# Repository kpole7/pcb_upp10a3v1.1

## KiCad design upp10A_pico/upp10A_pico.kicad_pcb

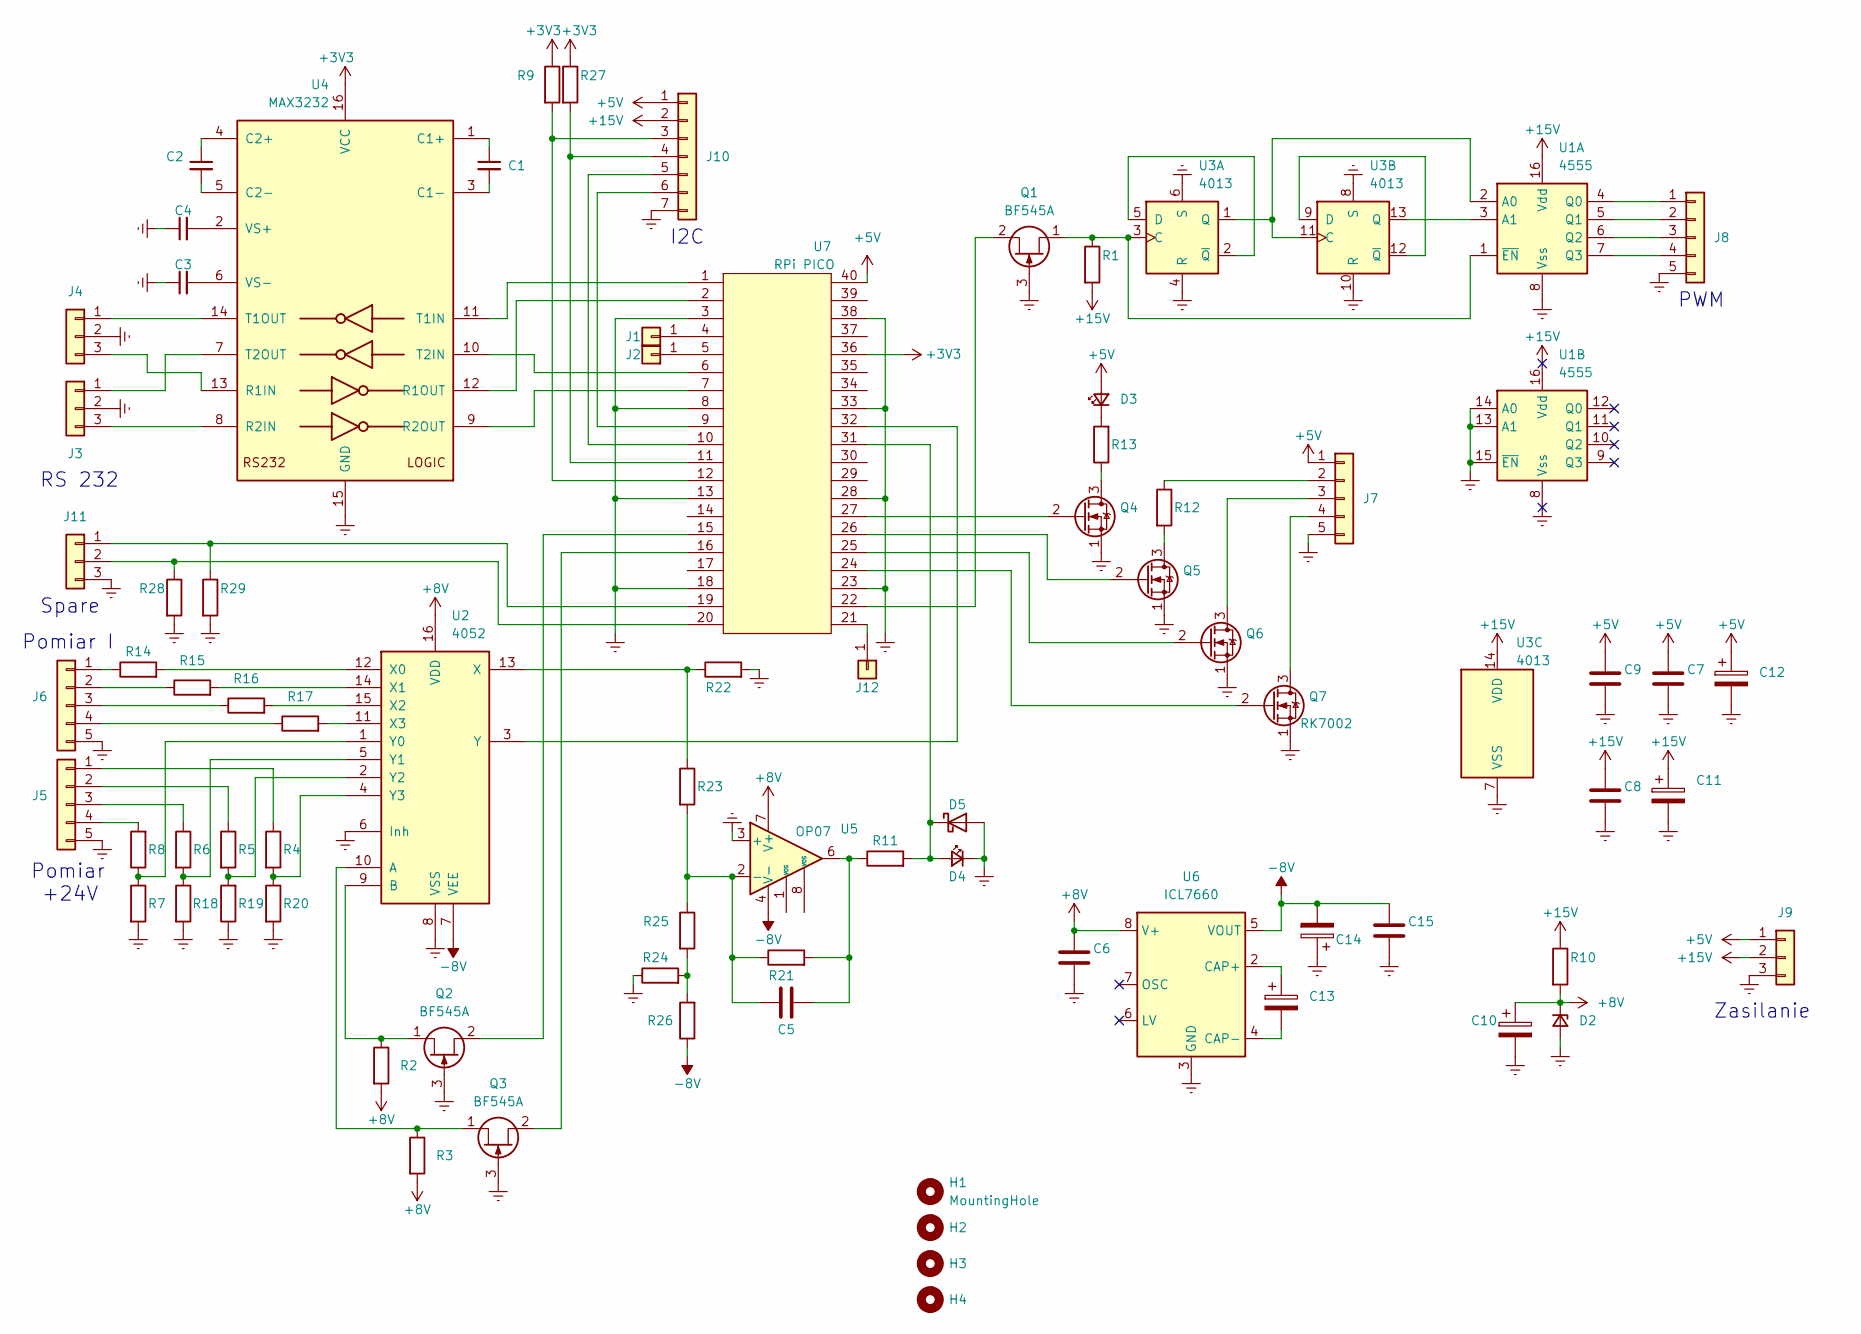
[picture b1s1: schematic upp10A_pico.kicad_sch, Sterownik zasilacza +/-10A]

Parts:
C1, C2, C3, C4: C_Small; C_0805_2012Metric_Pad1.18x1.45mm_HandSolder
C5: C; R_0805_2012Metric_Pad1.20x1.40mm_HandSolder
C6, C7, C8, C9, C15: C; C_0805_2012Metric_Pad1.18x1.45mm_HandSolder
C10, C11, C12, C13, C14: C_Polarized; CP_Radial_D6.3mm_P2.50mm
D2: D_Zener_Small; D_DO-34_SOD68_P7.62mm_Horizontal
D3: LED_Small; D_0805_2012Metric_Pad1.15x1.40mm_HandSolder
D4: LED_Small; D_5KP_P10.16mm_Horizontal
D5: BAT41; D_DO-35_SOD27_P7.62mm_Horizontal
H1, H2, H3, H4: MountingHole; MountingHole_3.2mm_M3_Pad
J1, J2, J12: Conn_01x01; Pin_D1.0mm_L10.0mm
J3, J4, J9, J11: Conn_01x03; PinHeader_1x03_P2.54mm_Vertical
J5, J6, J7, J8: Conn_01x05; PinHeader_1x05_P2.54mm_Vertical
J10: Conn_01x07; PinHeader_1x07_P2.54mm_Vertical
Q1, Q2, Q3: BF545A; SOT-23
Q4, Q5, Q6, Q7: RK7002; SOT-23
R1, R2, R3, R4, R5, R6, R7, R8, R9, R10, R11, R12, R13, R14, R15, R16, R17, R18, R19, R20, R21, R22, R23, R24, R25, R26, R27, R28, R29: R; R_0805_2012Metric_Pad1.20x1.40mm_HandSolder
U1: 4555; DIP-16_W7.62mm
U2: 4052; DIP-16_W8.89mm_SMDSocket_LongPads
U3: 4013; DIP-14_W7.62mm
U4: MAX3232; SOIC-16_3.9x9.9mm_P1.27mm
U5: OP07; DIP-8_W7.62mm
U6: ICL7660; DIP-8_W7.62mm
U7: RPi PICO; DIP-40_W700mils

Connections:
+3V3: R9.1, R27.1, U4.16 (VCC), U7.36
+5V: C7.1, C9.1, C12.1, D3.2 (A), J7.1, J9.1, J10.1, U7.40
+8V: C6.1, C10.1, D2.1 (K), R2.2, R3.2, R10.2, U2.16 (VDD), U5.7 (V+), U6.8 (V+)
+15V: C8.1, C11.1, J9.2, J10.2, R1.2, R10.1, U1.16 (Vdd), U3.14 (VDD)
-8V: C14.2, C15.1, R26.1, U2.7 (VEE), U5.4 (V-), U6.5 (VOUT)
GNDREF: C3.1, C4.1, C6.2, C7.2, C8.2, C9.2, C10.2, C11.2, C12.2, C14.1, C15.2, D2.2 (A), D4.1 (K), D5.2 (A), J3.2, J4.2, J5.5, J6.5, J7.5, J8.5, J9.3, J10.7, J11.3, Q1.3 (G), Q2.3 (G), Q3.3 (G), Q4.1 (S), Q5.1 (S), Q6.1 (S), Q7.1 (S), R7.2, R18.2, R19.1, R20.2, R22.2, R24.1, R28.2, R29.2, U1.8 (Vss), U1.13 (A1), U1.14 (A0), U1.15 (~EN), U2.6 (Inh), U2.8 (VSS), U3.4 (R), U3.6 (S), U3.7 (VSS), U3.8 (S), U3.10 (R), U4.15 (GND), U5.3 (+), U6.3 (GND), U7.3, U7.8, U7.13, U7.18, U7.23, U7.28, U7.33, U7.38
unnamed: C5.2, R11.1, R21.2, U5.6
unnamed: D3.1 (K), R13.2
unnamed: D4.2 (A), D5.1 (K), R11.2, U7.31
unnamed: J1.1, U7.4
unnamed: J2.1, U7.5
unnamed: J3.1, U4.7 (T2OUT)
unnamed: J3.3, U4.8 (R2IN)
unnamed: J4.1, U4.14 (T1OUT)
unnamed: J4.3, U4.13 (R1IN)
unnamed: J5.1, R4.1
unnamed: J5.2, R5.1
unnamed: J5.3, R6.1
unnamed: J5.4, R8.2
unnamed: J6.1, R14.1
unnamed: J6.2, R15.1
unnamed: J6.3, R16.1
unnamed: J6.4, R17.1
unnamed: J7.2, R12.1
unnamed: J7.3, Q6.3 (D)
unnamed: J7.4, Q7.3 (D)
unnamed: J8.1, U1.4 (Q0)
unnamed: J8.2, U1.5 (Q1)
unnamed: J8.3, U1.6 (Q2)
unnamed: J8.4, U1.7 (Q3)
unnamed: J10.3, R9.2, U7.12
unnamed: J10.4, R27.2, U7.11
unnamed: J10.5, U7.10
unnamed: J10.6, U7.9
unnamed: J11.1, R29.1, U7.19
unnamed: J11.2, R28.1, U7.20
unnamed: J12.1, U7.21
unnamed: Q1.2 (D), U7.22
unnamed: Q1.1 (S), R1.1, U1.1 (~EN), U3.3 (C)
unnamed: Q2.2 (D), U7.15
unnamed: Q2.1 (S), R2.1, U2.9 (B)
unnamed: Q3.2 (D), U7.16
unnamed: Q3.1 (S), R3.1, U2.10 (A)
unnamed: Q4.3 (D), R13.1
unnamed: Q4.2 (G), U7.27
unnamed: Q5.3 (D), R12.2
unnamed: Q5.2 (G), U7.26
unnamed: Q6.2 (G), U7.25
unnamed: Q7.2 (G), U7.24
unnamed: R24.2, R25.2, R26.2
unnamed: U1.2 (A0), U3.1 (Q), U3.11 (C)
unnamed: U1.3 (A1), U3.13 (Q)
unnamed: R14.2, U2.12 (X0)
unnamed: R15.2, U2.14 (X1)
unnamed: R16.2, U2.15 (X2)
unnamed: R17.2, U2.11 (X3)
unnamed: R22.1, R23.1, U2.13 (X)
unnamed: R7.1, R8.1, U2.1 (Y0)
unnamed: R6.2, R18.1, U2.5 (Y1)
unnamed: R5.2, R19.2, U2.2 (Y2)
unnamed: R4.2, R20.1, U2.4 (Y3)
unnamed: U2.3 (Y), U7.32
unnamed: U3.2 (~Q), U3.5 (D)
unnamed: U3.9 (D), U3.12 (~Q)
unnamed: C1.1, U4.1 (C1+)
unnamed: C1.2, U4.3 (C1-)
unnamed: C2.1, U4.4 (C2+)
unnamed: C2.2, U4.5 (C2-)
unnamed: U4.12 (R1OUT), U7.2
unnamed: U4.9 (R2OUT), U7.7
unnamed: U4.11 (T1IN), U7.1
unnamed: U4.10 (T2IN), U7.6
unnamed: C4.2, U4.2 (VS+)
unnamed: C3.2, U4.6 (VS-)
unnamed: C5.1, R21.1, R23.2, R25.1, U5.2 (-)
unnamed: C13.1, U6.2 (CAP+)
unnamed: C13.2, U6.4 (CAP-)

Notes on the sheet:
Pomiar +24V
Zasilanie
I2C
Spare
RS 232
Pomiar I
PWM

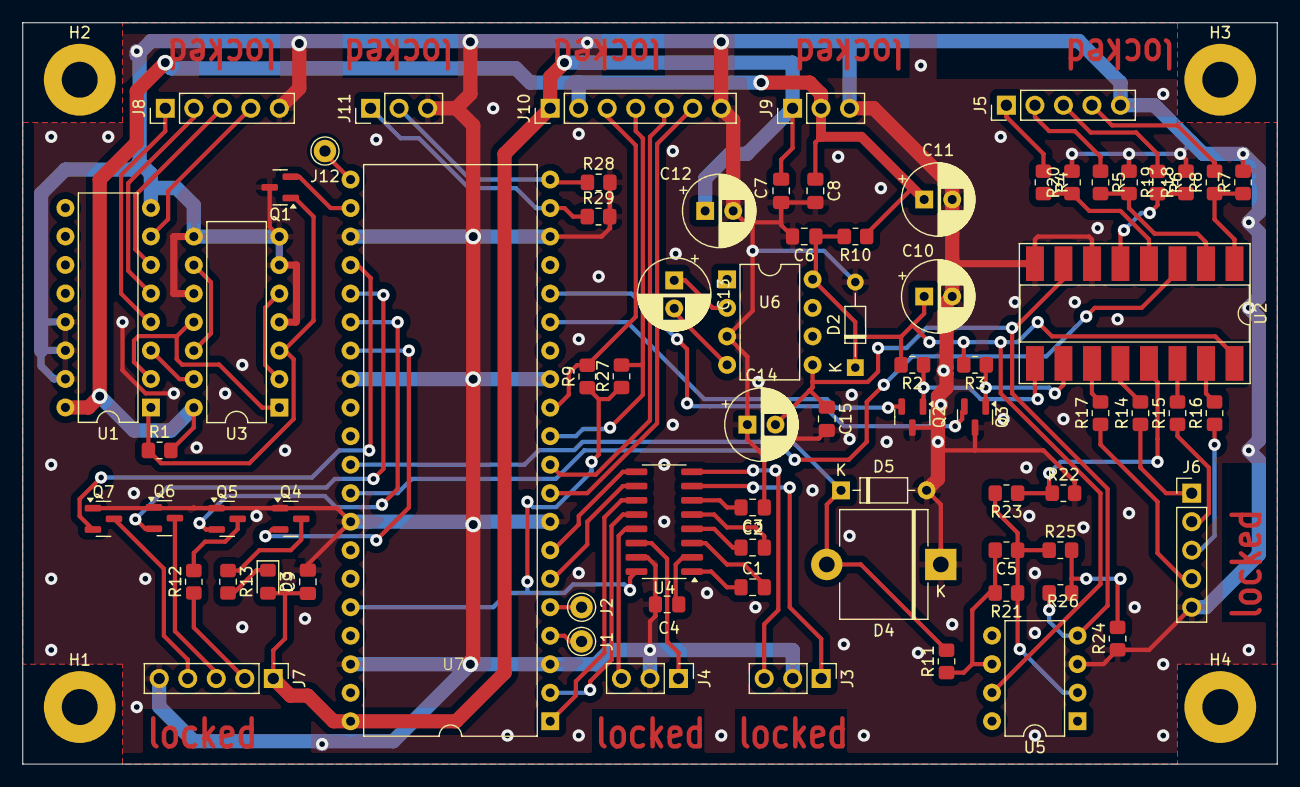
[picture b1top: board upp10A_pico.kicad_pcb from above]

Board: 2 copper layers, 111.8 x 66.0 mm, 78 parts (0 on the bottom side), 77 nets.

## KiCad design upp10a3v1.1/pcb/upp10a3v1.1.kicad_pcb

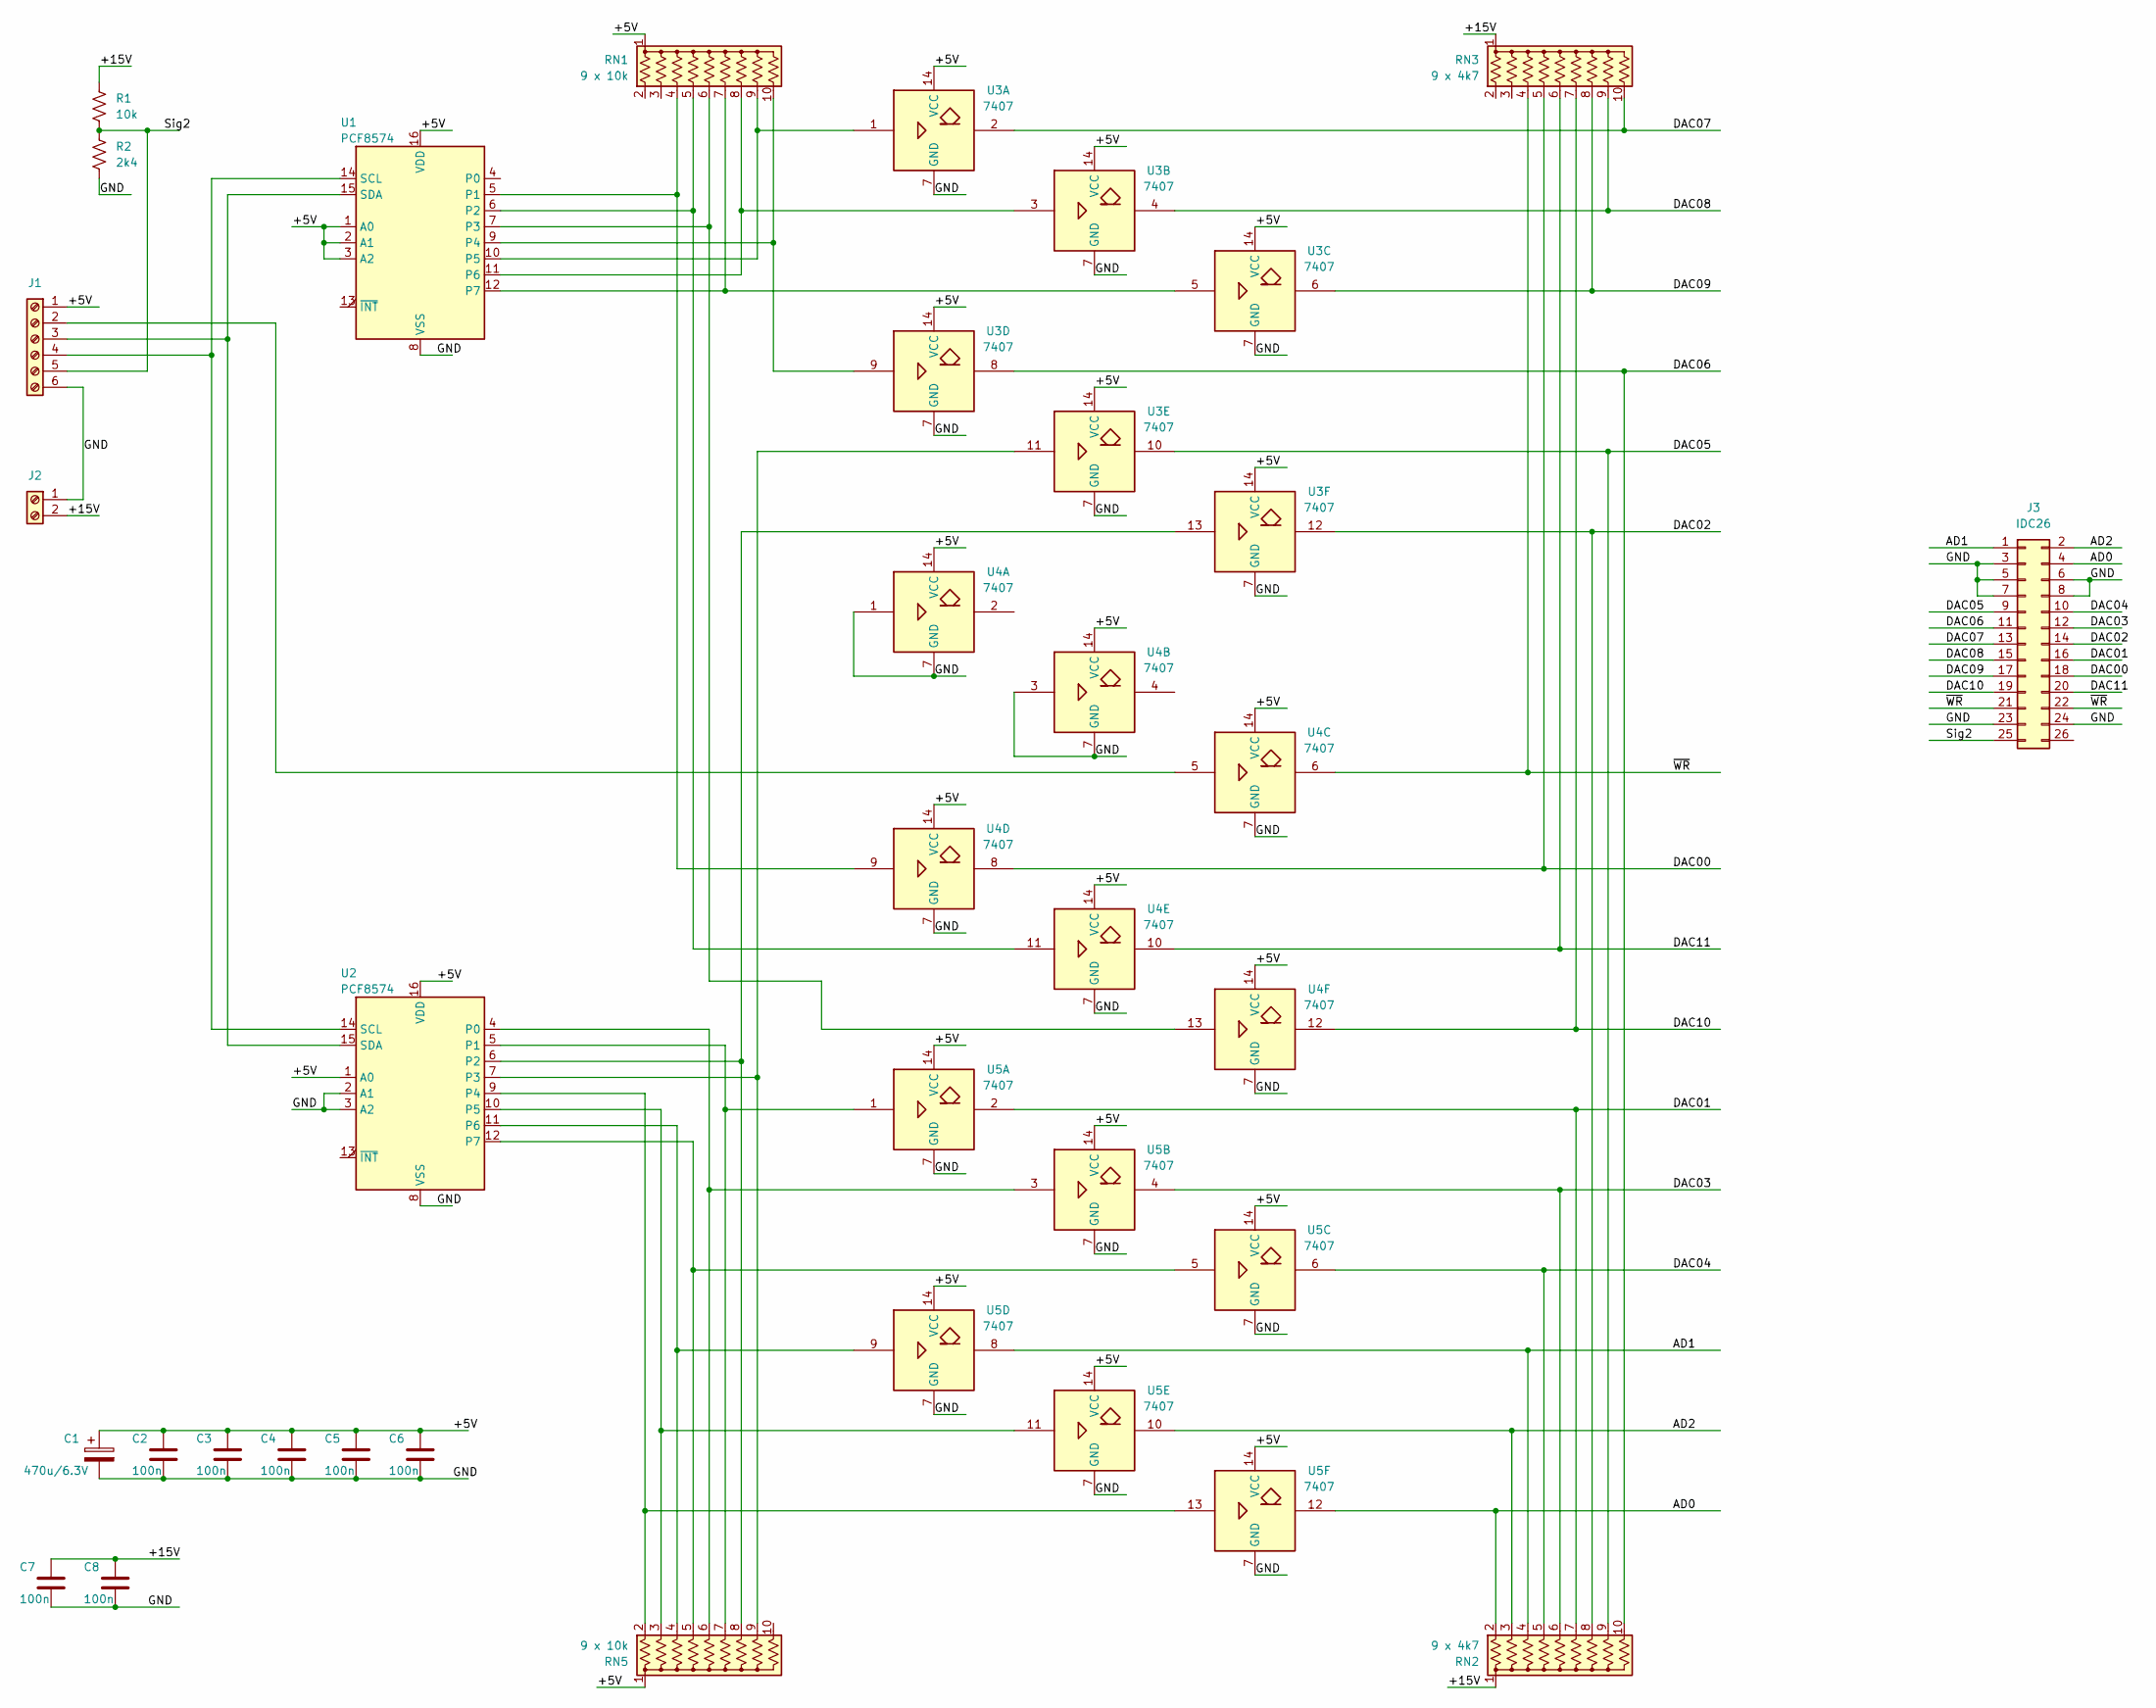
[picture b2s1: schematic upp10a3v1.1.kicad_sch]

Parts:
C1: 470u/6.3V; CP_Radial_D6.3mm_P2.50mm
C2, C3, C4, C5, C6, C7, C8: 100n; C_1206_3216Metric_Pad1.33x1.80mm_HandSolder
J1: Screw_Terminal_01x06; PhoenixContact_MCV_1,5_6-G-3.5_1x06_P3.50mm_Vertical
J2: Screw_Terminal_01x02; PhoenixContact_MCV_1,5_2-G-3.5_1x02_P3.50mm_Vertical
J3: IDC26; IDC-Header_2x13_P2.54mm_Vertical
R1: 10k; R_1206_3216Metric_Pad1.30x1.75mm_HandSolder
R2: 2k4; R_1206_3216Metric_Pad1.30x1.75mm_HandSolder
RN1, RN5: 9 x 10k; R_Array_SIP10
RN2, RN3: 9 x 4k7; R_Array_SIP10
U1, U2: PCF8574; SOIC-16W_7.5x10.3mm_P1.27mm
U3, U4, U5: 7407; CERDIP-14_W7.62mm_SideBrazed

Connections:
/+5V: C1.1, C2.1, C3.1, C4.1, C5.1, C6.1, J1.1, RN1.1 (common), RN5.1 (common), U1.1 (A0), U1.2 (A1), U1.3 (A2), U1.16 (VDD), U2.1 (A0), U2.16 (VDD), U3.14 (VCC), U4.14 (VCC), U5.14 (VCC)
/+15V: C7.1, C8.1, J2.2, R1.1, RN2.1 (common), RN3.1 (common)
/AD0: J3.4, RN2.2 (R1), U5.12
/AD1: J3.1, RN2.4 (R3), U5.8
/AD2: J3.2, RN2.3 (R2), U5.10
/DAC00: J3.18, RN3.5 (R4), U4.8
/DAC01: J3.16, RN2.7 (R6), U5.2
/DAC02: J3.14, RN2.8 (R7), U3.12
/DAC03: J3.12, RN2.6 (R5), U5.4
/DAC04: J3.10, RN2.5 (R4), U5.6
/DAC05: J3.9, RN2.9 (R8), U3.10
/DAC06: J3.11, RN2.10 (R9), U3.8
/DAC07: J3.13, RN3.10 (R9), U3.2
/DAC08: J3.15, RN3.9 (R8), U3.4
/DAC09: J3.17, RN3.8 (R7), U3.6
/DAC10: J3.19, RN3.7 (R6), U4.12
/DAC11: J3.20, RN3.6 (R5), U4.10
/GND: C1.2, C2.2, C3.2, C4.2, C5.2, C6.2, C7.2, C8.2, J1.6, J2.1, J3.3, J3.5, J3.6, J3.7, J3.8, J3.23, J3.24, R2.2, U1.8 (VSS), U2.2 (A1), U2.3 (A2), U2.8 (VSS), U3.7 (GND), U4.1, U4.3, U4.7 (GND), U5.7 (GND)
/Sig2: J1.5, J3.25, R1.2, R2.1
/~WR: J3.21, J3.22, RN3.4 (R3), U4.6
unnamed: J1.2, U4.5
unnamed: J1.3, U1.15 (SDA), U2.15 (SDA)
unnamed: J1.4, U1.14 (SCL), U2.14 (SCL)
unnamed: RN1.4 (R3), U1.5 (P1), U4.9
unnamed: RN1.5 (R4), U1.6 (P2), U4.11
unnamed: RN1.6 (R5), U1.7 (P3), U4.13
unnamed: RN1.7 (R6), U1.12 (P7), U3.5
unnamed: RN1.8 (R7), U1.11 (P6), U3.3
unnamed: RN1.9 (R8), U1.10 (P5), U3.1
unnamed: RN1.10 (R9), U1.9 (P4), U3.9
unnamed: RN5.2 (R1), U2.9 (P4), U5.13
unnamed: RN5.3 (R2), U2.10 (P5), U5.11
unnamed: RN5.4 (R3), U2.11 (P6), U5.9
unnamed: RN5.5 (R4), U2.12 (P7), U5.5
unnamed: RN5.6 (R5), U2.4 (P0), U5.3
unnamed: RN5.7 (R6), U2.5 (P1), U5.1
unnamed: RN5.8 (R7), U2.6 (P2), U3.13
unnamed: RN5.9 (R8), U2.7 (P3), U3.11

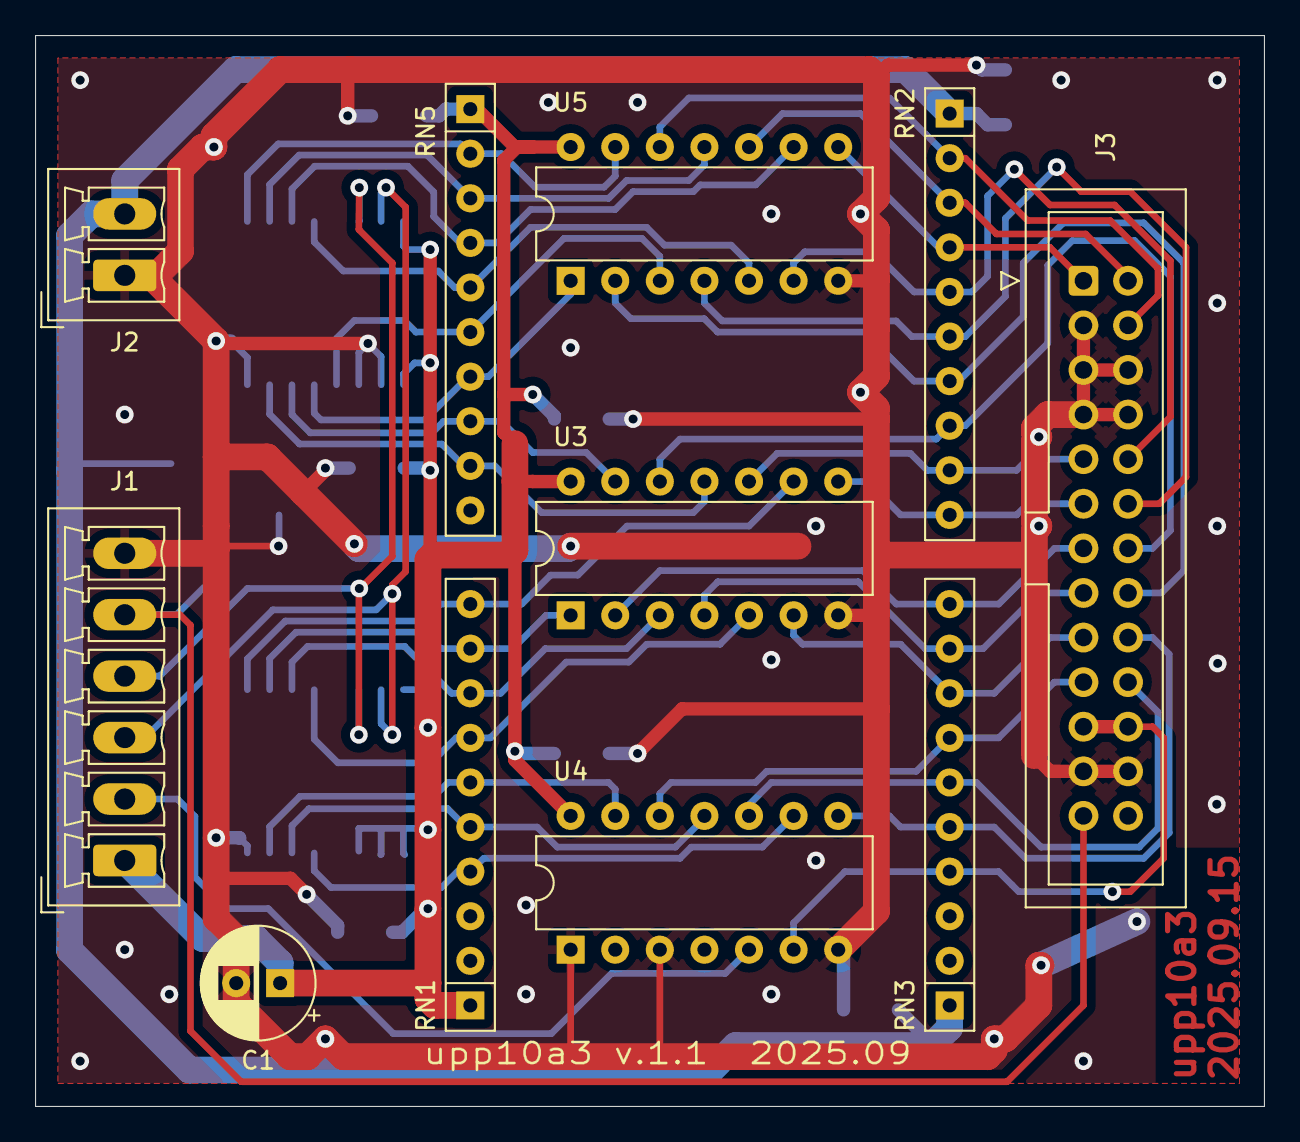
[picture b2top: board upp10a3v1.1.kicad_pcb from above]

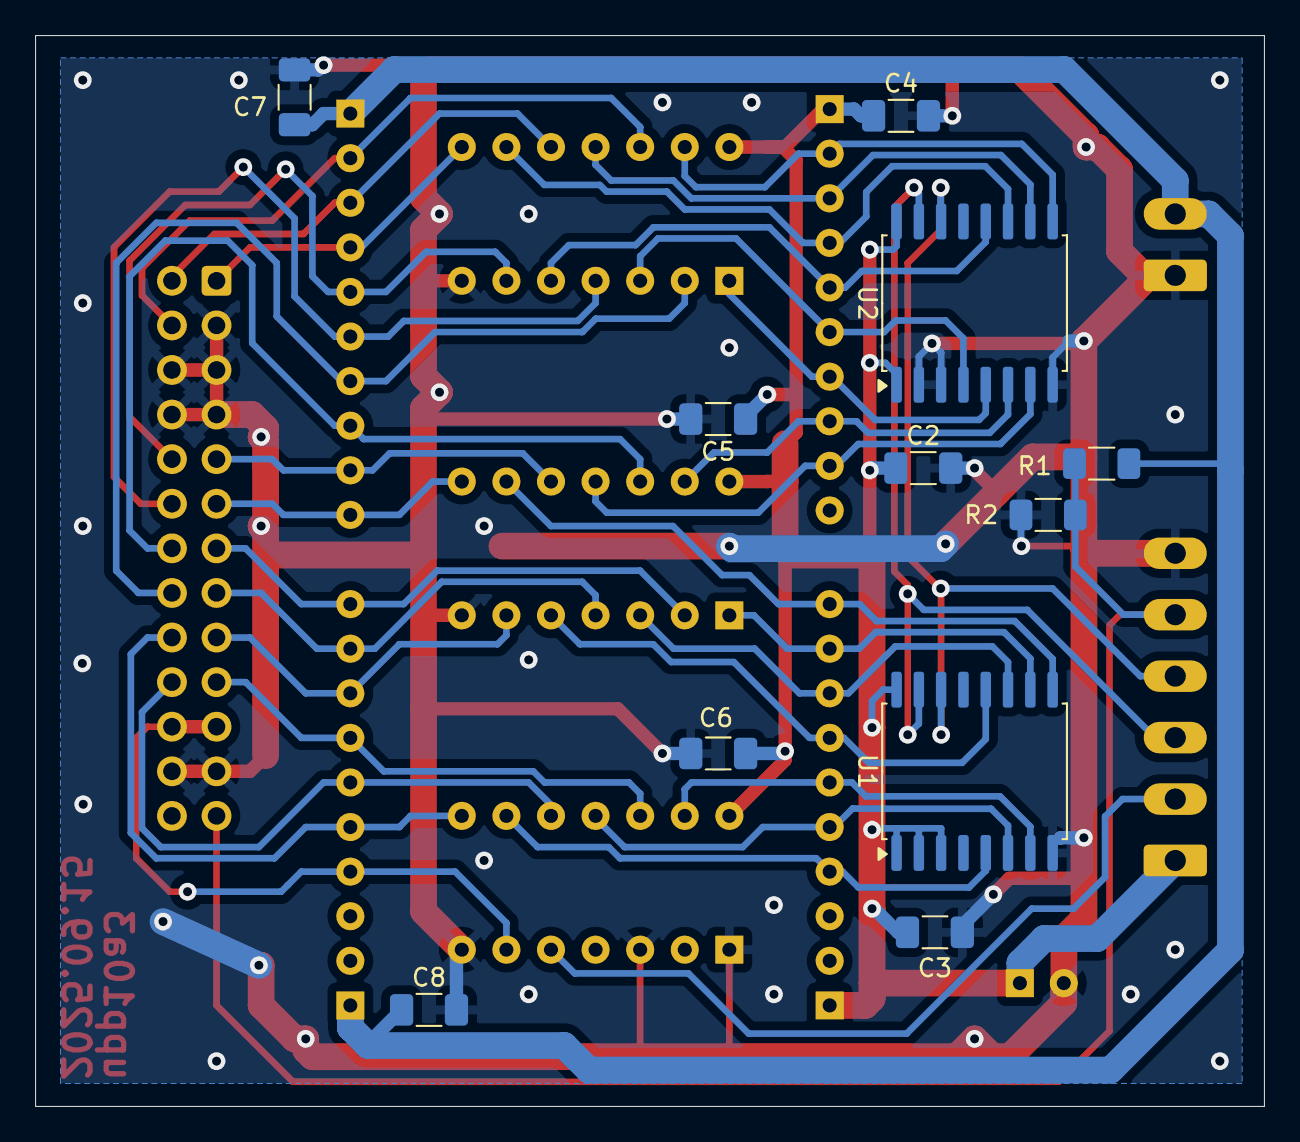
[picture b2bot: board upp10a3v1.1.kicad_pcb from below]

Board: 2 copper layers, 70.0 x 61.0 mm, 22 parts (11 on the bottom side), 38 nets.

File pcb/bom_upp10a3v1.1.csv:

"#","Reference","Qty","Value","Footprint","DNP"
"1","C1","1","470u/6.3V","Capacitor_THT:CP_Radial_D6.3mm_P2.50mm",""
"2","C2, C3, C4, C5, C6, C7, C8","7","100n","Capacitor_SMD:C_1206_3216Metric_Pad1.33x1.80mm_HandSolder",""
"3","J1","1","Screw_Terminal_01x06","Connector_Phoenix_MC:PhoenixContact_MCV_1,5_6-G-3.5_1x06_P3.50mm_Vertical",""
"4","J2","1","Screw_Terminal_01x02","Connector_Phoenix_MC:PhoenixContact_MCV_1,5_2-G-3.5_1x02_P3.50mm_Vertical",""
"5","J3","1","IDC26","Connector_IDC:IDC-Header_2x13_P2.54mm_Vertical",""
"6","R1","1","10k","Resistor_SMD:R_1206_3216Metric_Pad1.30x1.75mm_HandSolder",""
"7","R2","1","2k4","Resistor_SMD:R_1206_3216Metric_Pad1.30x1.75mm_HandSolder",""
"8","RN1, RN5","2","9 x 10k","Resistor_THT:R_Array_SIP10",""
"9","RN2, RN3","2","9 x 4k7","Resistor_THT:R_Array_SIP10",""
"10","U1, U2","2","PCF8574","Package_SO:SOP-16_3.9x9.9mm_P1.27mm",""
"11","U3, U4, U5","3","7407","Package_DIP:CERDIP-14_W7.62mm_SideBrazed",""

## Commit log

2025-09-12 Initial commit; project of pcb; part of the interface to PSU;
2025-09-12 PCB project cont. Gerber files generated;
2025-09-15 Some corrections made;
2025-09-16 Cleanup;
2025-09-16 Reorganization of directory tree;
2025-09-16 Added some documentation;
2025-09-24 Added assembly drawing, comments and calculations.
2025-09-29 Assembly drawing;
2025-10-03 Added new pcb project "main power witch";
2025-11-05 Added a new pcb project from Mr. Janek's e-mail;
2025-11-05 Correction in PCB project;
2025-11-05 PCB: components layout;
2025-11-06 PCB routing completed;
2025-11-12 Made corrections on PCB; added gerber files; added schematic in pdf;
2025-11-12 Added price calculation;
2025-11-12 Added assembly drawing;
2025-11-12 Forgotten file for the previous commit;
2025-11-20 Added invoice;
